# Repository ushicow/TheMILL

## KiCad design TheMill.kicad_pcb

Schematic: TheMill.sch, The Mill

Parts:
BUS1: A2_BUS; BUS_A2
C1, C2, C3, C4, C5, C6, C7, C8: C; C_Disc_D4.3mm_W1.9mm_P5.00mm
C9, C10: 47pF; C_Disc_D4.3mm_W1.9mm_P5.00mm
R1, R3: 2.2k; R_Axial_DIN0207_L6.3mm_D2.5mm_P10.16mm_Horizontal
R2: 470; R_Axial_DIN0207_L6.3mm_D2.5mm_P10.16mm_Horizontal
R4, R5: 240; R_Axial_DIN0207_L6.3mm_D2.5mm_P10.16mm_Horizontal
U1: 74LS32; DIP-14_W7.62mm_Socket
U2: 74LS08; DIP-14_W7.62mm_Socket
U3: 74LS266; DIP-14_W7.62mm_Socket
U4: 74LS74; DIP-14_W7.62mm_Socket
U5: 74LS30; DIP-14_W7.62mm_Socket
U6: 74LS14; DIP-14_W7.62mm_Socket
U7: MC6809E; DIP-40_W15.24mm_Socket
U8: 74LS259; DIP-16_W7.62mm_Socket
U9, U10: 74LS245; DIP-20_W7.62mm_Socket
U11: 2716; DIP-24_W15.24mm_Socket
U12, U13, U14: 74LS367; DIP-16_W7.62mm_Socket

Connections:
+5V: BUS1.25, C1.1, C2.1, C3.1, C5.1, C6.1, C7.1, C8.1, R1.1, R2.1, R3.1, U1.14, U2.14, U3.14, U4.1, U4.4, U4.10, U4.13, U4.14, U5.11, U5.14, U6.14 (VCC), U7.7, U8.16, U9.20, U10.20, U11.21, U11.24, U12.16, U13.16, U14.16
/a0: BUS1.2, U8.1, U11.8, U13.13
/a1: BUS1.3, U8.2, U11.7, U13.3
/a2: BUS1.4, U8.3, U11.6, U12.11
/a3: BUS1.5, U11.5, U12.7
/a4: BUS1.6, U11.4, U12.3
/a5: BUS1.7, U11.3, U13.5
/a6: BUS1.8, U11.2, U13.11
/a7: BUS1.9, U11.1, U13.9
/a8: BUS1.10, U11.23, U12.13
/a9: BUS1.11, U11.22, U12.5
/a10: BUS1.12, U11.19, U12.9
/a11: BUS1.13, U3.8, U13.7
/a12: BUS1.14, U5.4, U5.5, U14.5
/a13: BUS1.15, U5.3, U14.11
/a14: BUS1.16, U5.2, U14.3
/a15: BUS1.17, U5.1, U14.13
/d0: U7.31, U9.2, U10.18, U11.9
/d1: U7.30, U9.3, U10.17, U11.10
/d2: U7.29, U9.4, U10.16, U11.11
/d3: U7.28, U9.5, U10.15, U11.13
/d4: U7.27, U9.6, U10.14, U11.14
/d5: U7.26, U9.7, U10.13, U11.15
/d6: U7.25, U9.8, U10.12, U11.16
/d7: U7.24, U8.13, U9.9, U10.11, U11.17
/da0: BUS1.49, U10.2
/da1: BUS1.48, U10.3
/da2: BUS1.47, U10.4
/da3: BUS1.46, U10.5
/da4: BUS1.45, U10.6
/da5: BUS1.44, U10.7
/da6: BUS1.43, U10.8
/da7: BUS1.42, U10.9
GND: BUS1.26, C1.2, C2.2, C3.2, C5.2, C6.2, C7.2, C8.2, C9.2, C10.2, U1.7, U2.7, U3.7, U3.9, U3.12, U4.7, U5.7, U6.7 (GND), U7.1, U7.39, U8.8, U9.1, U9.10, U10.10, U11.12, U12.8, U13.8, U14.8, U14.10
unnamed: BUS1.18, U1.5, U2.1, U6.11, U14.7
unnamed: BUS1.22, U2.5, U14.9
unnamed: BUS1.30, U3.11
unnamed: BUS1.31, U8.15
unnamed: BUS1.37, R4.2
unnamed: BUS1.40, R5.2
unnamed: BUS1.41, U1.4, U1.12, U2.2
unnamed: C9.1, R5.1, U6.3
unnamed: C10.1, R4.1, U6.1
unnamed: R1.2, U3.4, U14.14
unnamed: R2.2, U6.6, U7.34
unnamed: R3.2, U3.10, U11.18
unnamed: U1.1, U2.3
unnamed: U1.2, U2.6
unnamed: U1.3, U10.1
unnamed: U1.6, U8.14
unnamed: U1.11, U9.19
unnamed: U1.13, U2.4, U6.10
unnamed: U2.11, U7.40
unnamed: U2.12, U8.5, U9.17
unnamed: U2.13, U7.37, U8.6, U9.16
unnamed: U3.5, U8.12
unnamed: U3.6, U7.23
unnamed: U3.13, U8.4, U9.18
unnamed: U4.3, U6.2
unnamed: U4.5, U7.35
unnamed: U4.9, U5.12
unnamed: U4.2, U4.11, U6.4, U6.5
unnamed: U4.12, U7.36
unnamed: U5.6, U8.11
unnamed: U7.2, U8.7, U9.15
unnamed: U7.3, U8.10, U9.13
unnamed: U7.4, U8.9, U9.14
unnamed: U7.5, U9.12
unnamed: U7.6, U9.11
unnamed: U6.12, U10.19
unnamed: U5.8, U6.13, U11.20
unnamed: U4.8, U12.1, U12.15, U13.1, U13.15, U14.1, U14.15
unnamed: U7.12, U12.2
unnamed: U7.17, U12.4
unnamed: U7.11, U12.6
unnamed: U7.18, U12.10
unnamed: U7.10, U12.12
unnamed: U7.16, U12.14
unnamed: U7.9, U13.2
unnamed: U7.13, U13.4
unnamed: U7.19, U13.6
unnamed: U7.15, U13.10
unnamed: U7.14, U13.12
unnamed: U7.8, U13.14
unnamed: U7.22, U14.2
unnamed: U7.20, U14.4
unnamed: U7.32, U14.6
unnamed: U7.21, U14.12

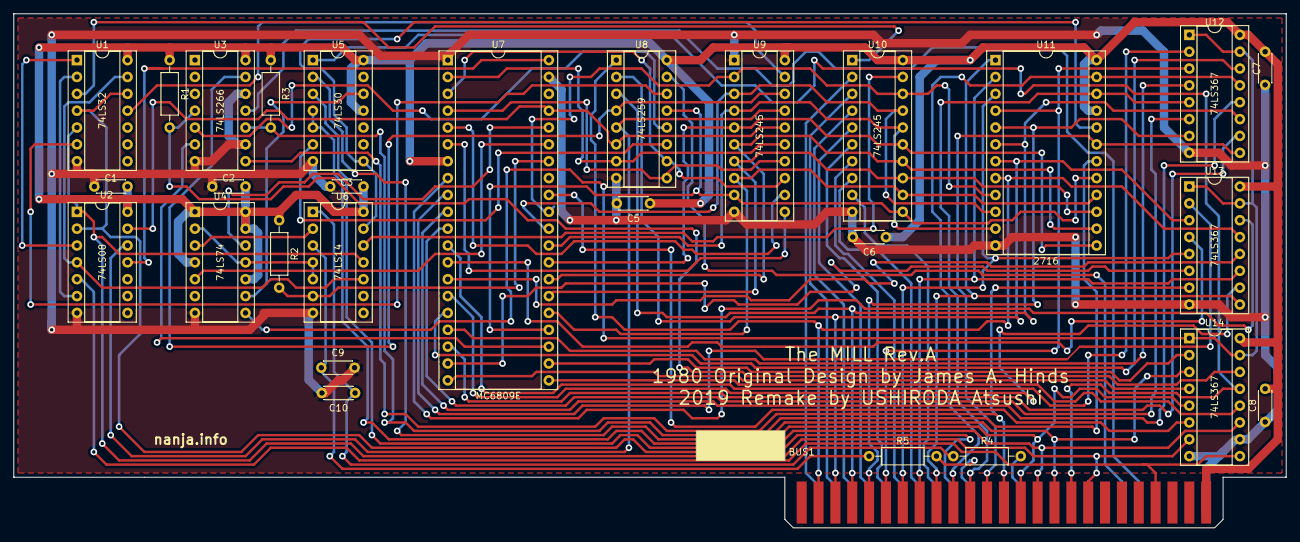
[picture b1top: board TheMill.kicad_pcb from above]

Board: 2 copper layers, 191.8 x 77.5 mm, 29 parts (0 on the bottom side), 88 nets.

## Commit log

2018-10-13 init
2019-01-03 20190101 pcb ordered
